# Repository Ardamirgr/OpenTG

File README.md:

<div align="center">

# OpenTG

**Open-source automotive electronics for monitoring, control, ECU communication, and calibration.**

Originally developed for the **Hyundai Coupe / Tiburon**, with many projects designed to be adaptable to other vehicles, ECUs, and custom engine-management setups.

[Support OpenTG](https://www.paypal.com/donate/?hosted_button_id=CYKH5WKZKP4M2)

</div>

---

## Projects

### OpenTG AFR Meter

A complete wideband AFR/lambda system based on the **Bosch LSU 4.9** sensor and **Bosch CJ125** interface IC.

**Wideband controller**

- LSU 4.9 sensor and heater control
- CAN bus output
- Configurable analog AFR/lambda output
- Narrowband and wideband signal emulation

**Digital gauge**

- TFT display with AFR, lambda, oxygen concentration, and sensor-temperature views
- Configurable LED bar
- On-device menu and EEPROM-stored settings
- CAN communication with the controller

---

### OpenTG Boost Controller

A configurable electronic boost-control system for turbocharged vehicles using a MAC-style boost-control solenoid.

- Closed-loop boost control
- Boost targets by RPM and gear
- Multiple selectable boost profiles
- MAP and intake-air-temperature measurement
- CAN-based RPM and vehicle-speed input
- Optional analog inputs
- Overboost protection
- Exhaust-gas-temperature support
- Dedicated TFT gauge and user interface

---

### KLT120 K-Line / L-Line Transceiver

An open-source discrete automotive **K-Line / L-Line transceiver** designed for communication with ECUs and other diagnostic modules using **ISO 9141, ISO 14230 / KWP2000**, and manufacturer-specific K-Line protocols.

Unlike conventional designs based on dedicated K-Line transceiver ICs, the KLT120 uses **LM393B comparators** and discrete N-channel MOSFET line drivers.

Key features include:

* Automotive **K-Line** interface
* Automotive **L-Line** interface
* Independent K-Line and L-Line control
* Selectable **3.3V or 5V MCU logic** depending on the fitted LDO
* Direct interface with microcontroller UART peripherals
* Support for conventional **10.4 kbaud** diagnostic communication
* Support for **5-baud and fast initialization** methods
* Designed for reliable operation at **120 kbaud and beyond**
* Suitable for ECU diagnostics, flashing, logging, and reverse-engineering applications

---

### LTM43 Live Tuning Module

A live-calibration module designed specifically for the **Siemens SIMK43 ECU**.

The LTM43 replaces the original ECU flash memory with a removable module containing:

- **1 Mbit flash memory**, twice the capacity of the original 512 Kbit device
- **512 Kbit SRAM** connected in parallel with the flash memory
- A castellated pin-header adapter PCB that solders directly to the original flash footprint

> [!NOTE]
> The design is based on the live-calibration approach used by Siemens during ECU and engine development.

---

### SLCAN Adapter - Experimental

A compact CAN-to-USB serial interface for ECU flashing, diagnostics, logging, and calibration.

Typical uses include:

- SIMK43 communication
- ECU data logging
- CAN traffic monitoring
- LTM43 live tuning
- Use with compatible OpenTG and OpenGK tools

The adapter implements the **SLCAN protocol**, providing a low-cost alternative to commercial CAN interfaces for supported software.

---

### S4/RS4 MAF Adapter

An adapter board for integrating the Audi S4/RS4 B6 mass-airflow sensors with the stock SIMK43 ECU setups.

It provides a clean interface between the original harness connector and the MAF, without requiring any modifications.

Typical applications include:

- Turbo conversions
- Setups that exceed the measurement range of the original MAF sensor
- Replacement option if the stock MAF sensor can't be found from a reputable manufacturer (VDO, Continental).

---

### R8 COP Adapter

An ignition adapter board for converting the G4GC engines to Audi R8-style coil-on-plug ignition coils. This can theoretically work on any wasted-spark setup.

The board provides an organized interface between the factory engine harness and the replacement coils, simplifying wiring and installation.

> [!IMPORTANT]
> Coil compatibility and ignition strategy must be verified before installation. Depending on the ECU, the ignition dwell times WILL need to be changed, or the R8 Coils will be catastrophically damaged.
> For the G4GC dwell times of <2ms should be used. For most turbocharged setups 1.4-1.6ms is enough.

---

### Oil Temperature / Oil Pressure Gauge

A planned standalone gauge for monitoring engine-oil temperature and pressure.

**Status:** Under development. Have a prototype made from a modified Gauge unit, but no proper hardware design.

---

## Repository Contents

Depending on the project, each directory may include:

| Category | Contents |
|---|---|
| **Hardware** | Schematics, PCB layouts, Gerbers, BOMs, and assembly notes |
| **Firmware** | Embedded source code, binaries, and flashing instructions |
| **Wiring** | Pinouts, connection diagrams, and installation guidance |
| **Calibration** | Configuration files, lookup data, and setup notes |
| **Mechanical** | Enclosure, mounting, or other fabrication files |

Refer to the README inside each project directory for project-specific instructions.

---

## Intended Use

OpenTG projects are intended for enthusiasts, developers, motorsport applications, research, and education.

They may require fine-pitch soldering, ECU disassembly, firmware flashing, automotive electrical knowledge, and engine-management calibration experience.

> [!WARNING]
> Incorrect installation, wiring, firmware, or calibration can damage the ECU, engine, sensors, wiring, or connected equipment. Verify pin assignments, supply voltages, grounding, firmware versions, and board revisions before powering any hardware.

---

## Contributing

Contributions, testing, bug reports, documentation improvements, and hardware revisions are welcome.

For useful bug reports, include the relevant hardware revision, firmware version or commit, vehicle and ECU type, wiring configuration, CAN bitrate, logs or measurements, and a clear description of the problem.

---

## License

See the LICENSE file present in the repository root for license information.

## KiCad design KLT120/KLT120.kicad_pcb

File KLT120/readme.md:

# KLT120

> **Open-source discrete K-Line / L-Line transceiver for 3.3V and 5V microcontrollers**

**KLT120** is a discrete automotive **K-Line / L-Line transceiver** designed for interfacing microcontrollers with **ISO 9141**, **ISO 14230 / KWP2000**, and manufacturer-specific diagnostic buses.

Instead of relying on a dedicated K-Line transceiver IC, KLT120 uses **LM393B comparators** together with discrete **N-channel MOSFET line drivers**.

Depending on the fitted LDO, the logic side of the board can operate at either **3.3V or 5V**, allowing the same PCB to interface with a wide range of microcontrollers.

KLT120 is designed around a **120 kbaud target**, with additional headroom possible depending on bus capacitance, wiring, and the connected ECU. It remains fully suitable for traditional **10.4 kbaud K-Line communication**, **5-baud initialization**, and **fast initialization**.

---

## Features

| Feature | Description |
|---|---|
| **K-Line** | Full transmit and receive support |
| **L-Line** | Independent transmit and receive support |
| **Logic voltage** | 3.3V or 5V, selected by LDO choice |
| **PHY architecture** | LM393B comparators + discrete N-channel MOSFETs |
| **RX threshold** | Battery-referenced, approximately 0.5 × VBAT |
| **Bus pull-up** | Approximately 510–520 Ω tester-side pull-up |
| **Target speed** | 120 kbaud |
| **Protocols** | ISO 9141, ISO 14230 / KWP2000, manufacturer-specific K-Line |
| **Initialization** | 5-baud init and fast init |
| **Supply** | Automotive VBAT with protection and regulated logic rail |

---

## Logic Voltage

KLT120 can be configured for either **3.3V** or **5V** logic by fitting the appropriate LDO.

| LDO | Logic Rail |
|---|---:|
| `TLV7603` | `3.3V` |
| `TLV7605` | `5.0V` |

Throughout the design, this regulated logic rail is referred to as:

```text
VLOGIC
```

The selected logic voltage is used for:

- RX output pull-ups
- TX input logic levels
- Comparator TX reference generation

This allows the same PCB to be used with both modern **3.3V MCUs** and traditional **5V microcontrollers**.

---

## Architecture

Each diagnostic line consists of two main sections:

1. **Transmit driver**
2. **Receive comparator**

K-Line and L-Line are controlled independently.

```text
LM393B #1
├── K-Line TX
└── K-Line RX

LM393B #2
├── L-Line TX
└── L-Line RX
```

L-Line reception is optional in applications where only L-Line transmission is required.

---

## Transmit Path

The transmit stage uses one LM393B comparator as both an **inverter** and **logic-level detector**.

A reference voltage equal to approximately half of the selected logic voltage is generated from `VLOGIC`:

```text
TX_REF ≈ VLOGIC / 2
```

For example:

```text
3.3V logic → TX_REF ≈ 1.65V
5.0V logic → TX_REF ≈ 2.50V
```

The MCU transmit signal is connected to the inverting comparator input:

```text
MCU TX  -------- LM393B (-)
TX_REF  -------- LM393B (+)
```

Because the LM393B output is **open collector**, the MOSFET gate pull-up voltage can be chosen independently from the comparator supply voltage.

The comparator output drives an N-channel MOSFET used as a low-side K/L-Line switch.

### TX Logic

| MCU TX | MOSFET | K/L Line |
|---:|:---:|:---:|
| `HIGH` | OFF | HIGH / released |
| `LOW` | ON | LOW / dominant |

This preserves normal UART polarity.

When UART TX is idle (`HIGH`), the MOSFET remains OFF and the diagnostic line is released.

---

## K-Line / L-Line Output Stage

Each diagnostic line is pulled toward vehicle battery voltage through approximately **510–520 Ω** on the tester side.

The pull-up is implemented using **three 1206 resistors in series** to spread the power dissipation.

```text
VBAT
 |
~510–520 Ω
 |
 +------------- K/L LINE
 |
Drain
 NMOS
Source
 |
GND
```

At a vehicle charging voltage of **14.5V** and a **520 Ω** pull-up:

```text
I = 14.5 / 520
I ≈ 27.9 mA

P = V² / R
P ≈ 0.40 W
```

The line-driver MOSFET therefore only needs to sink roughly **30 mA** during a dominant LOW state.

Suitable SOT-23 N-channel MOSFETs include:

- `2N7002K`
- `BSS123`

Important MOSFET characteristics are:

- Sufficient `VDS` rating
- Sufficient `VGS` rating
- Low gate charge
- Ability to sink at least ~30 mA
- Suitable switching behavior at the selected gate voltage

Very low `RDS(on)` is not required because the bus current is relatively small.

---

## Receiver

The receive stage uses the second comparator in each LM393B.

Instead of comparing the diagnostic line against a fixed voltage, the receiver threshold is derived from **VBAT**. This keeps the switching point proportional to the actual K/L-Line HIGH level.

The diagnostic-line input is divided before reaching the comparator:

```text
VLINE_SENSE = VLINE / 4
```

The reference input is derived from VBAT:

```text
VREF = VBAT / 8
```

The comparator changes state when:

```text
VLINE / 4 = VBAT / 8
```

Therefore:

```text
VLINE = VBAT / 2
```

So the resulting receive threshold is approximately:

```text
VTH ≈ 0.5 × VBAT
```

This battery-referenced threshold is similar in principle to the input architecture used by dedicated automotive K-Line transceiver ICs.

---

## RX Logic Output

Because the LM393B output is **open collector**, the RX output can be pulled directly to the selected logic rail.

Depending on the fitted LDO, the MCU therefore receives either:

```text
0 / 3.3V
```

or:

```text
0 / 5.0V
```

No additional RX level shifter is required.

---

## K-Line and L-Line

K-Line is normally used for bidirectional communication between the diagnostic tester and ECU.

L-Line is primarily associated with initialization and wake-up on older ISO 9141 / KWP2000 systems.

KLT120 keeps both lines independent, allowing firmware to implement:

- K-Line-only communication
- K + L initialization
- 5-baud initialization
- Fast initialization
- Manufacturer-specific wake-up sequences
- Independent K-Line / L-Line monitoring

For applications that do not require L-Line reception, the `L_RX` comparator may be left unused.

---

## Baud Rate

KLT120 is designed around a target communication speed of:

```text
120 kbaud
```

At 120000 baud:

```text
Tbit = 1 / 120000
Tbit ≈ 8.33 µs
```

The LM393B propagation delay under large input overdrive is on the order of hundreds of nanoseconds, while the MOSFET switching time is significantly shorter.

The main limitation at higher baud rates is normally the **LOW-to-HIGH transition** of the diagnostic bus.

When the MOSFET releases the line, the pull-up resistor must charge the total bus capacitance.

The approximate RC time constant is:

```text
τ = R × C
```

With a 510–520 Ω pull-up:

| Bus Capacitance | Approx. RC Time Constant |
|---:|---:|
| `1 nF` | `~0.52 µs` |
| `5 nF` | `~2.60 µs` |
| `10 nF` | `~5.20 µs` |

The actual maximum usable baud rate depends on:

- Vehicle wiring
- Diagnostic cable length
- ECU input capacitance
- Protection components
- Connector capacitance
- Number of devices connected to the bus

Traditional **10.4 kbaud** K-Line operation has a very large timing margin.

> **120 kbaud is the intended design target, not a guarantee for every possible vehicle harness.**

---

## Why a Discrete Transceiver?

Dedicated K-Line transceiver ICs are convenient, but some parts can be difficult to source, relatively expensive, or inconvenient when working with configurable MCU logic levels.

KLT120 implements the basic automotive diagnostic PHY using common components:

```text
Comparator
    +
MOSFET
    +
Resistors
    +
Protection
```

This makes the design:

- Easy to understand
- Easy to modify
- Easy to repair
- Flexible with component selection
- Compatible with both 3.3V and 5V systems
- Well suited to custom diagnostic hardware

It also allows the receive threshold, output drive, pull-up strength, and protection circuitry to be adapted for specific applications.

---

## Applications

KLT120 can be used for:

- Automotive diagnostic interfaces
- ECU flashing tools
- ECU reverse engineering
- KWP2000 communication
- ISO 9141 communication
- ECU bench harnesses
- ESP32-based diagnostic tools
- AVR-based diagnostic tools
- STM32-based diagnostic tools
- Data logging equipment
- Manufacturer-specific K-Line protocols
- 5-baud initialization
- Fast initialization
- Development and research hardware

---

## Project Status

> **KLT120 is currently under development.**

The hardware should be considered experimental until it has been validated against multiple ECUs, vehicles, wiring configurations, baud rates, and automotive transient conditions.

Testing is intended to cover both standard KWP2000 communication speeds and higher-speed K-Line implementations.

---

## Disclaimer

This project is intended for **development, research, diagnostic, and educational use**.

Automotive electrical systems can generate high-energy voltage transients. Incorrect connections may damage the interface, ECU, vehicle electronics, or connected development hardware.

**Use at your own risk.**

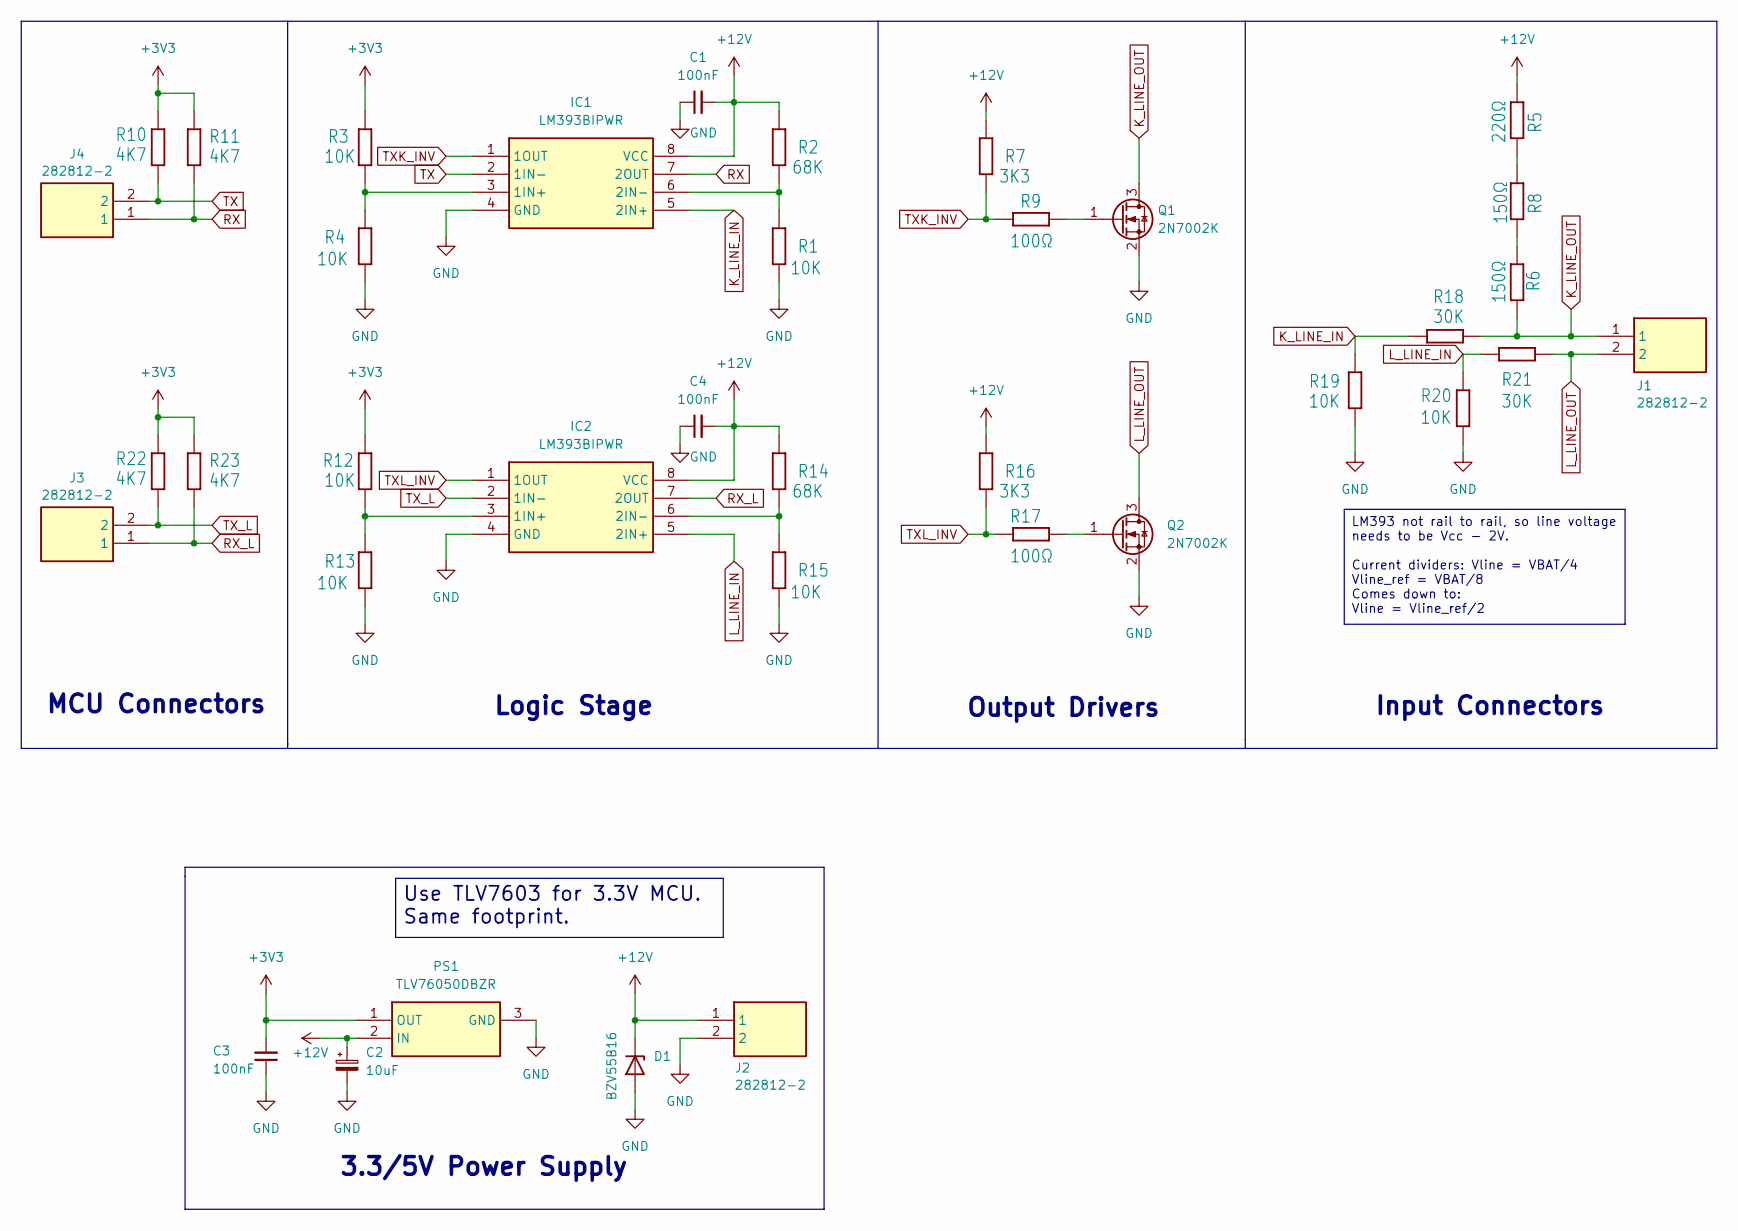
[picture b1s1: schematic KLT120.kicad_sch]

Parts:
C1, C3, C4: 100nF; C_0805_2012Metric
C2: 10uF; CP_Elec_5x5.7
D1: BZV55B16; D_MiniMELF
IC1, IC2: LM393BIPWR; SOP65P640X120-8N; Mouser Part Number 595-LM393BIPWR
J1, J2, J3, J4: 282812-2; 2828122; Mouser Part Number 571-282812-2
PS1: TLV76050DBZR; SOT95P237X112-3N; Mouser Part Number 595-TLV76050DBZR
Q1, Q2: 2N7002K; SOT-23
R1, R3, R4, R12, R13, R15, R19, R20: 10K; R_0805_2012Metric_Pad1.20x1.40mm_HandSolder
R2, R14: 68K; R_0805_2012Metric_Pad1.20x1.40mm_HandSolder
R5: 220Ω; R_1206_3216Metric_Pad1.30x1.75mm_HandSolder
R6, R8: 150Ω; R_1206_3216Metric_Pad1.30x1.75mm_HandSolder
R7, R16: 3K3; R_0805_2012Metric_Pad1.20x1.40mm_HandSolder
R9, R17: 100Ω; R_0805_2012Metric_Pad1.20x1.40mm_HandSolder
R10, R11, R22, R23: 4K7; R_0805_2012Metric_Pad1.20x1.40mm_HandSolder
R18, R21: 30K; R_0805_2012Metric_Pad1.20x1.40mm_HandSolder

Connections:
+3V3: C3.2, PS1.1 (OUT), R3.2, R10.2, R11.2, R12.2, R22.2, R23.2
+12V: C1.2, C2.1, C4.2, D1.1 (K), IC1.8 (VCC), IC2.8 (VCC), J2.1, PS1.2 (IN), R2.2, R5.2, R7.2, R14.2, R16.2
GND: C1.1, C2.2, C3.1, C4.1, D1.2 (A), IC1.4 (GND), IC2.4 (GND), J2.2, PS1.3 (GND), Q1.2 (S), Q2.2 (S), R1.1, R4.1, R13.1, R15.1, R19.1, R20.1
K_LINE_IN: IC1.5 (2IN+), R18.2, R19.2
K_LINE_OUT: J1.1, Q1.3 (D), R6.1, R18.1
L_LINE_IN: IC2.5 (2IN+), R20.2, R21.2
L_LINE_OUT: J1.2, Q2.3 (D), R21.1
unnamed: IC1.3 (1IN+), R3.1, R4.2
unnamed: IC1.6 (2IN-), R1.2, R2.1
unnamed: IC2.3 (1IN+), R12.1, R13.2
unnamed: IC2.6 (2IN-), R14.1, R15.2
unnamed: Q1.1 (G), R9.1
unnamed: Q2.1 (G), R17.1
unnamed: R5.1, R8.2
unnamed: R6.2, R8.1
RX: IC1.7 (2OUT), J4.1, R11.1
RX_L: IC2.7 (2OUT), J3.1, R23.1
TX: IC1.2 (1IN-), J4.2, R10.1
TXK_INV: IC1.1 (1OUT), R7.1, R9.2
TXL_INV: IC2.1 (1OUT), R16.1, R17.2
TX_L: IC2.2 (1IN-), J3.2, R22.1

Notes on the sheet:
Output Drivers
Logic Stage
Input Connectors
MCU Connectors
3.3/5V Power Supply
LM393 not rail to rail, so line voltage needs to be Vcc - 2V. Current dividers: Vline = VBAT/4 Vline_ref = VBAT/8 Comes down to: Vline = Vline_ref/2
Use TLV7603 for 3.3V MCU. Same footprint.

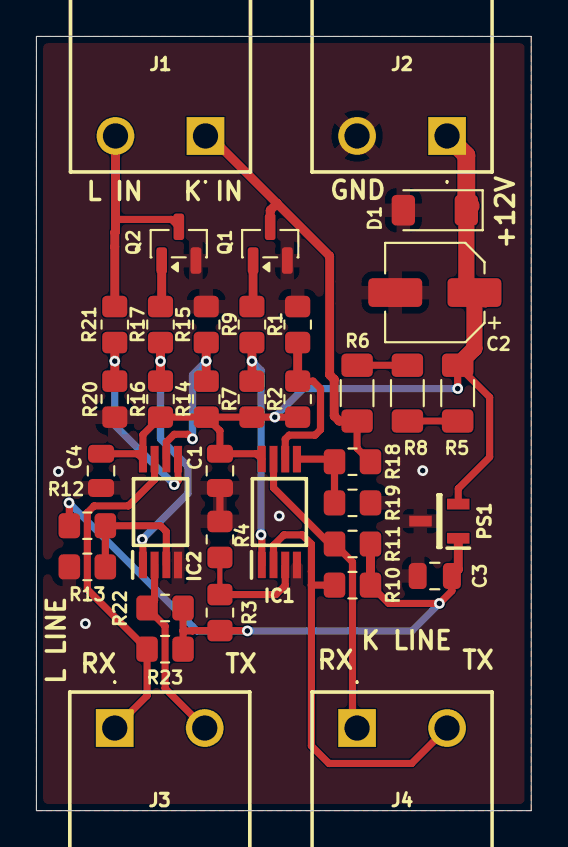
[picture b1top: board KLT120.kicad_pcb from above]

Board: 2 copper layers, 27.5 x 43.0 mm, 37 parts (0 on the bottom side), 21 nets.

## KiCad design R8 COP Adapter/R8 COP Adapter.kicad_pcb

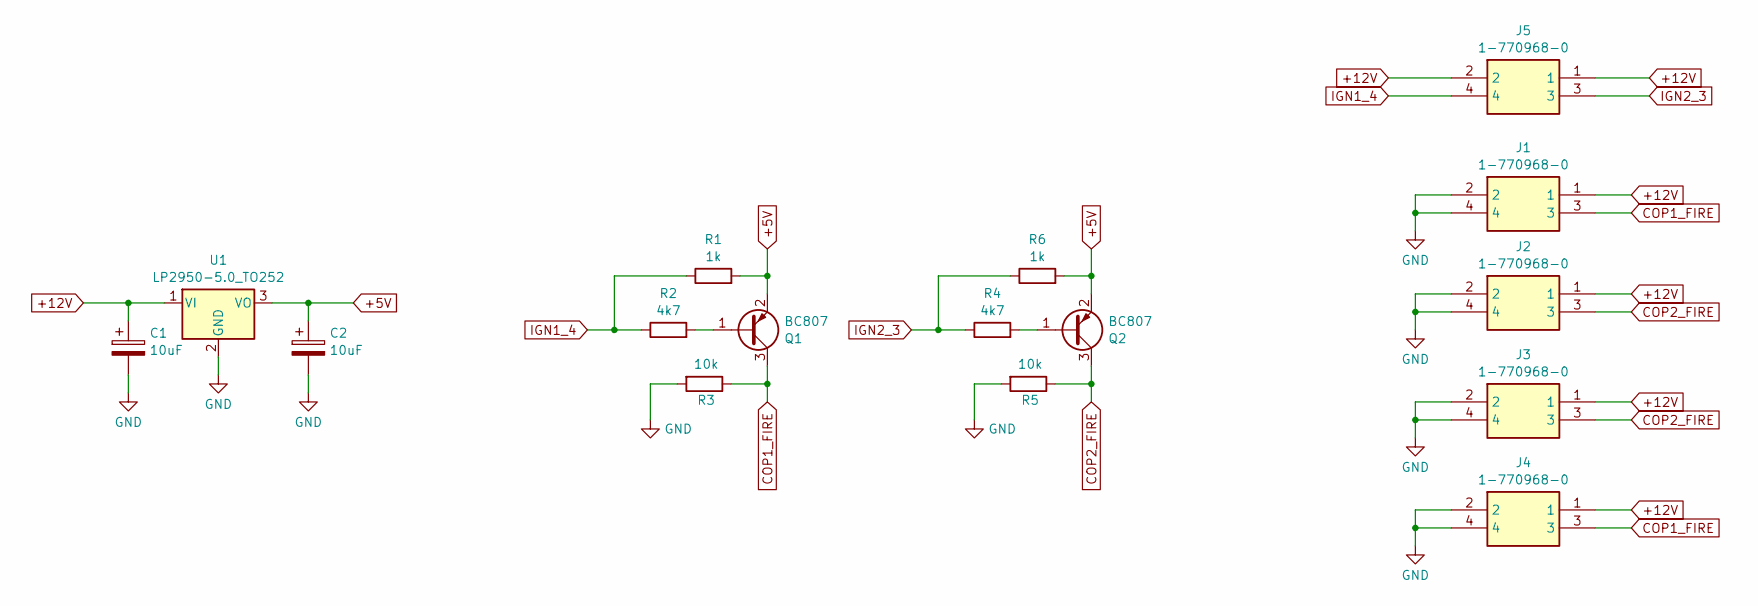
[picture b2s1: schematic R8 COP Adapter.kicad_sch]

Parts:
C1, C2: 10uF; CP_Radial_D5.0mm_P2.00mm
J1, J2, J3, J4, J5: 1-770968-0; 17709680; Mouser Part Number 571-1-770968-0
Q1, Q2: BC807; SOT-23
R1, R6: 1k; R_0805_2012Metric
R2, R4: 4k7; R_0805_2012Metric
R3, R5: 10k; R_0805_2012Metric
U1: LP2950-5.0_TO252; TO-252-2

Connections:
+5V: C2.1, Q1.2 (E), Q2.2 (E), R1.2, R6.2, U1.3 (VO)
+12V: C1.1, J1.1, J2.1, J3.1, J4.1, J5.1, J5.2, U1.1 (VI)
COP1_FIRE: J1.3, J4.3, Q1.3 (C), R3.1
COP2_FIRE: J2.3, J3.3, Q2.3 (C), R5.1
GND: C1.2, C2.2, J1.2, J1.4, J2.2, J2.4, J3.2, J3.4, J4.2, J4.4, R3.2, R5.2, U1.2 (GND); also elsewhere on the board
IGN1_4: J5.4, R1.1, R2.1
IGN2_3: J5.3, R4.1, R6.1
unnamed: Q1.1 (B), R2.2
unnamed: Q2.1 (B), R4.2

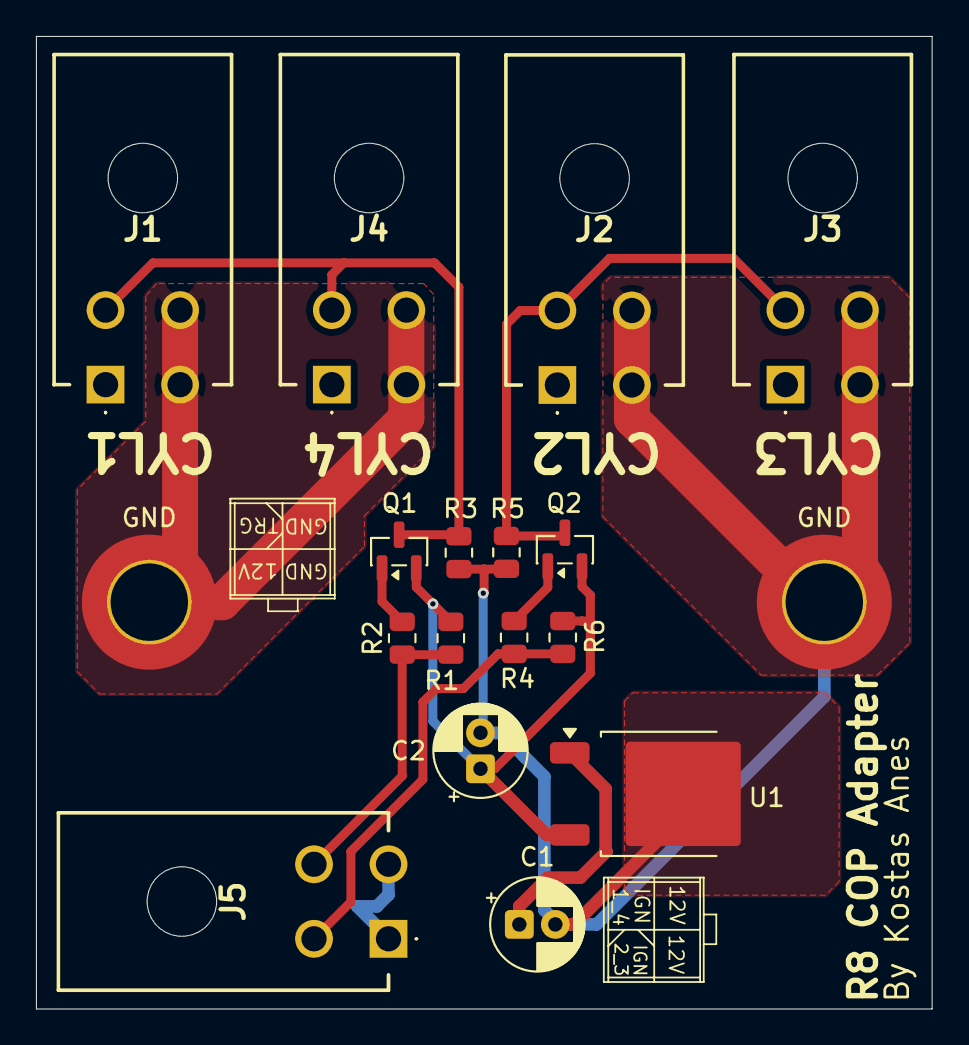
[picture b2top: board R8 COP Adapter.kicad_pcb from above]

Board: 2 copper layers, 49.8 x 54.0 mm, 18 parts (0 on the bottom side), 9 nets.

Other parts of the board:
GND: MountingHole_4.3mm_M4_DIN965_Pad_TopBottom
GND#2: MountingHole_4.3mm_M4_DIN965_Pad_TopBottom

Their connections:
GND: GND.1, GND#2.1; also elsewhere on the board

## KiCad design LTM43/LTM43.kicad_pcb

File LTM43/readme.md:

# LTM43 — Live Tuning Module for the Siemens SIMK43 ECU

LTM43 is a hardware module that enables live calibration changes on Siemens SIMK43 engine control units.

The module replaces the original flash memory fitted to the ECU. A small pin-header adapter PCB is soldered directly onto the original flash IC footprint, and the LTM43 plugs into this adapter through female headers.

> [!WARNING]
> This project requires fine-pitch soldering directly onto an automotive ECU PCB. Incorrect assembly, wiring, flashing, or use may permanently damage the ECU or prevent the engine from starting. Use the module only if you are familiar with ECU repair, boot-mode flashing, and automotive electrical systems.

## How It Works

The LTM43 contains:

- A **1 Mbit flash memory**, providing twice the capacity of the original 512 Kbit device.
- A **512 Kbit SRAM**, connected in parallel with the flash memory.

When the ECU starts in the required debug mode, the calibration data is copied from flash into SRAM. The ECU then operates from the SRAM copy, allowing calibration data to be modified while the ECU is running.

During shutdown, the modified SRAM contents are copied back into flash. The updated calibration is therefore retained and restored at the next startup.

This follows the live-tuning method used by Siemens during ECU and engine development.

## Hardware Overview

The system consists of two PCBs:

1. **Flash adapter board**  
   Soldered directly to the original flash IC pads on the SIMK43 ECU.

2. **LTM43 module**  
   Plugs into the adapter board through female pin headers and contains the replacement flash and SRAM devices.

## SRAM Options

The LTM43 PCB includes alternative SRAM footprints to support different packages. During assembly, populate **only one SRAM option**.

Supported devices are:

- Infineon `CY62128ELL-45ZXI`
- Infineon `CY62128ELL-45SXA`
- Renesas `R1LP0108ESN-5SI#B1`

## Board Assembly

The pin-header adapter board must sit completely flush against the ECU PCB so that its castellated edges can be soldered correctly to the original flash IC pads.

After installing and trimming the pin headers:

1. Cut the protruding header pins as close to the adapter PCB as practical.
2. Carefully sand the remaining pin ends until they are level with the underside of the PCB.
3. Confirm that no pin end prevents the adapter board from sitting flat.

For the LTM43 module, just solder the IC's and 100nF capacitors at their respective footprints. 
Remeber that the female headers should be placed on the bottom PCB side! 

> [!CAUTION]
> Do not force the adapter board flat while soldering. Any remaining pin protrusion can place mechanical stress on the ECU pads and may cause pad lifting or unreliable connections.

## Installation

1. Remove the original flash IC from the SIMK43 ECU.
2. Clean and inspect the exposed flash footprint.
3. Assemble the pin-header adapter as described above.
4. Align the castellated pads with the original flash footprint.
5. Check orientation and pin numbering before soldering (Pin#1 should be at the side of the C167 MCU).
6. Solder the adapter board to the ECU flash pads.
7. Solder a jumper wire from C167 Pin 88 (P4.3/A19 ) to the Adapter Board pin #3. This is best done from a via present on the bottom side of the ECU, that connects to Pin 88. 
8. Inspect every connection for bridges, incomplete joints, lifted pads, or misalignment.
9. Insert the LTM43 to the pin headers of the adapter board, observing the correct orientation (LTM43 oriented towards C167 MCU).
10. Perform an initial BSL flash to program the replacement flash memory.

## Initial BSL Flash

A blank replacement flash device must first be programmed through the SIMK43 boot-strapped loader, or **BSL**, interface.

The required firmware is:

```text
ca663057
```

It is available from the OpenGK SIMK repository:

- [OpenGK SIMK firmware repository](https://github.com/OpenGK-org/opengk-simk)

GKFlasher can be used to BSL flash and it is available here:

- [GKFlasher releases](https://github.com/Dante383/GKFlasher/releases)

### BSL Connection Method 1

1. Connect ECU pins **3, 14, 21, and 22** to **+12 V**.
2. Connect the diagnostic **K-Line** to ECU pin **77**, according to the ECU pinout.
3. Fit a **470 Ω resistor** to the ECU **W-Line**.
4. Splice the K-Line into the K-Line connection on the ECU header. When using a Y-split OBD2 cable, this is pin **9**.
5. Pull the **BOOT** pin to ground through a **10 kΩ resistor**.
6. Connect ECU power and ground.
7. Open the **BSL** tab in GKFlasher and begin the required operation.

### Alternative BSL Connection Method

Use this method when the first connection method does not work:

1. Connect ECU pins **3, 14, 21, and 22** to **+12 V**.
2. Connect OBD pin **7**, the K-Line, to ECU header pin **47**, the W-Line.
3. Pull flash-memory pin **28**, the BOOT pin, to ground through a **10 kΩ resistor**.
4. Connect ECU power and ground.
5. Open the **BSL** tab in GKFlasher and begin the required operation.

> [!IMPORTANT]
> Verify all ECU pin numbers against the correct SIMK43 connector and PCB documentation before applying power. Use a current-limited, fused 12 V supply for bench flashing.

## CAN Bus Communication

After the initial BSL flash, subsequent communication and calibration changes can be performed through CAN bus.

Supported interfaces include:

- A PCAN-compatible interface
- The OpenTG SLCAN Adapter

SLCAN Adapter project:

- [OpenTG SLCAN Adapter](https://github.com/Ardamirgr/OpenTG/tree/main/SLCAN_Adapter)

### CAN Wiring

Connect:

| Signal | SIMK43 ECU pin |
|---|---:|
| CAN High | 7 |
| CAN Low | 6 |
| Ground | ECU/interface shared ground |

A shared ground between the ECU and CAN interface is required.

### SLCAN Adapter Power

The SLCAN Adapter requires a regulated **5V supply**. It can be powered by either:

- The USB header, when the corresponding power-selection jumper is shorted.
- An external regulated 5V source, such as a suitable ECU-side supply.

Do not apply 12V directly to a 5V input.

## Recommended First Power-Up Procedure

Before connecting the ECU to a vehicle:

1. Inspect the adapter and LTM43 for solder bridges and incorrect component orientation.
2. Check resistance between all supply rails and ground for obvious short circuits.
3. Verify continuity from every ECU flash pad to the corresponding LTM43 signal.
5. Power the ECU from a fused, current-limited bench supply.
6. Perform the BSL flash using the `ca663057` firmware.
7. Power-cycle the ECU and verify CAN communication.
8. Confirm that calibration reads and writes operate correctly before vehicle installation.

## Removal and Serviceability

The LTM43 is removable after the flash-footprint adapter has been installed. This allows the module to be replaced or serviced without repeatedly soldering directly to the ECU flash pads.

Always disconnect ECU power before inserting or removing the LTM43.

## Disclaimer

This project is intended for development, research, motorsport, and off-road applications by experienced users.

The project contributors accept no responsibility for:

- ECU, engine, wiring, or vehicle damage
- Data corruption or failed flashing
- Unsafe engine calibration
- Emissions or road-legality violations
- Injury or property damage resulting from assembly or use

You are responsible for verifying the hardware, firmware, wiring, calibration, and legal suitability of the finished system.

## Related Projects

- [OpenGK SIMK](https://github.com/OpenGK-org/opengk-simk)
- [GKFlasher](https://github.com/Dante383/GKFlasher/releases)
- [OpenTG SLCAN Adapter](https://github.com/Ardamirgr/OpenTG/tree/main/SLCAN_Adapter)

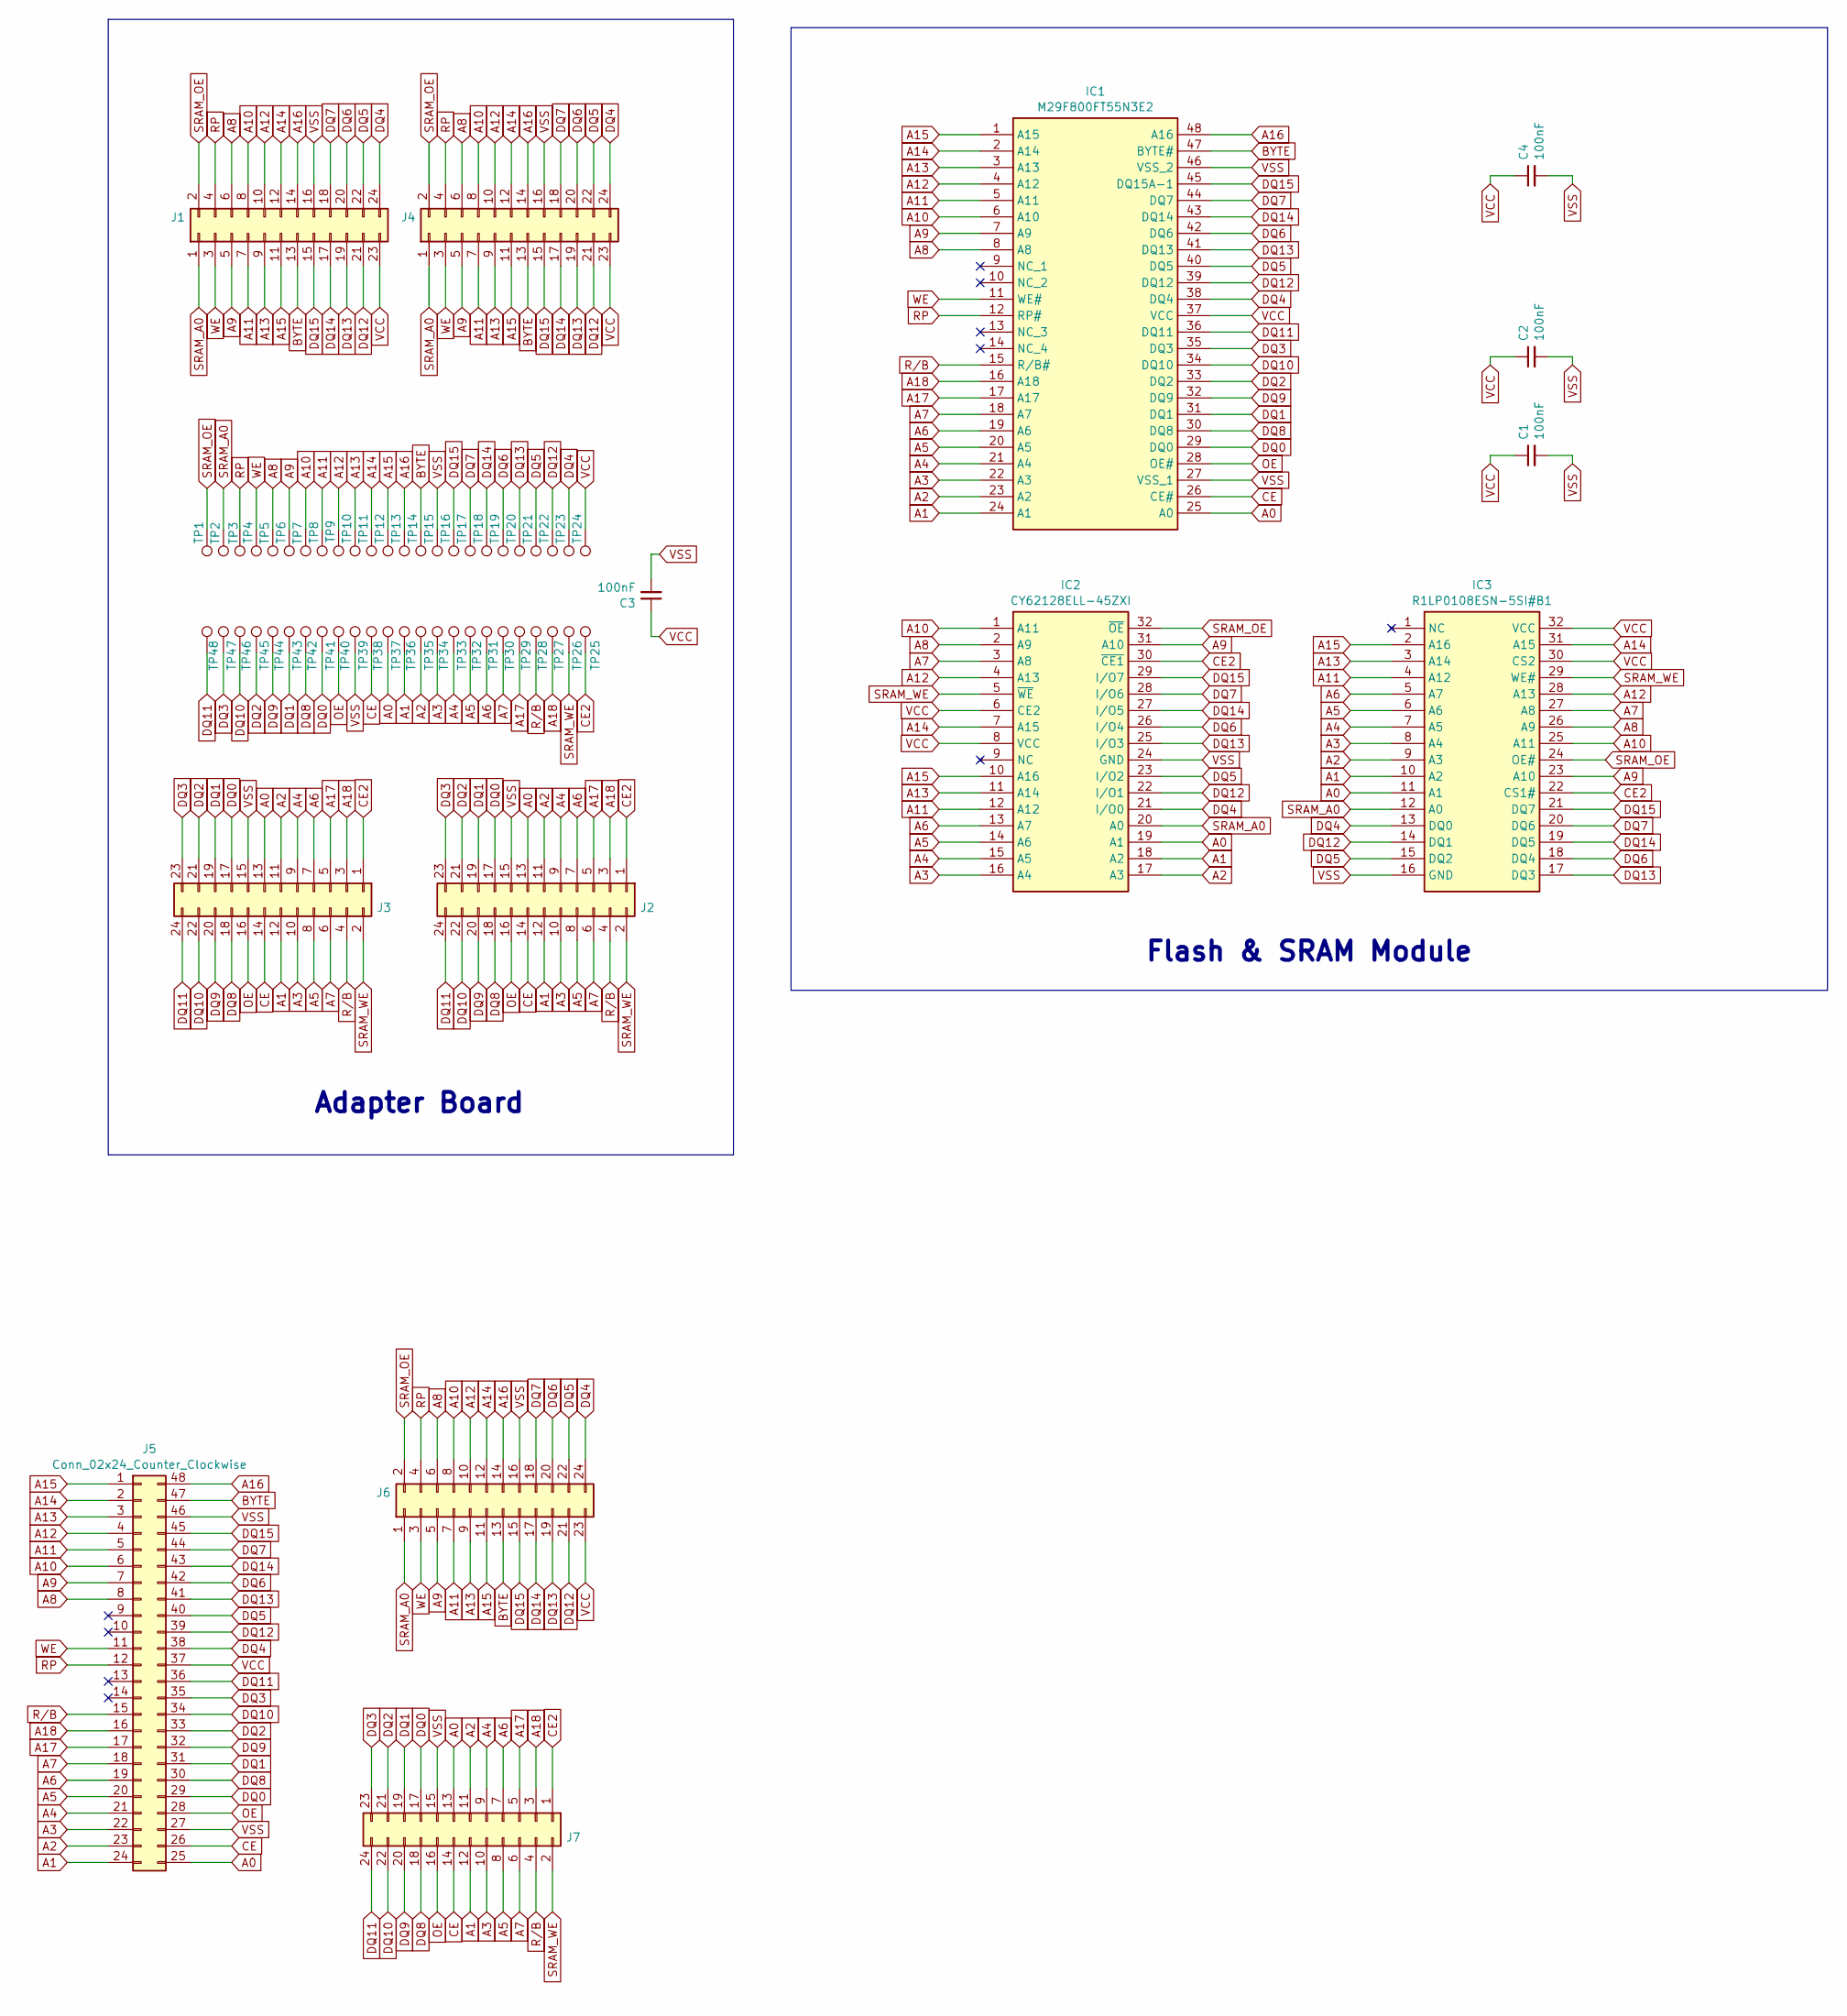
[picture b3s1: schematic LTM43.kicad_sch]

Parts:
C1, C2, C3, C4: 100nF; C_0805_2012Metric
IC1: M29F800FT55N3E2; SOP50P2000X120-48N; Mouser Part Number 913-M29F800FT55N3E2
IC2: CY62128ELL-45ZXI; SOP50P2000X120-32N; Mouser Part Number 727-CY62128ELL45ZXI
IC3: R1LP0108ESN-5SI#B1; SOIC127P1410X305-32N; Mouser Part Number 968-R1LP0108ESN5SIB1
J1, J2: Conn_02x12_Odd_Even
J3, J4: Conn_02x12_Odd_Even; PinSocket_2x12_P2.54mm_Vertical
J5: Conn_02x24_Counter_Clockwise; DIP-48_W15.24mm_Socket_LongPads
J6, J7: Conn_02x12_Odd_Even; PinHeader_2x12_P2.54mm_Vertical
TP1, TP2, TP3, TP4, TP5, TP6, TP7, TP8, TP9, TP10, TP11, TP12, TP13, TP14, TP15, TP16, TP17, TP18, TP19, TP20, TP21, TP22, TP23, TP24: TestPoint; TestPoint_THTPad_D1.0mm_Drill0.5mm
TP25, TP26, TP27, TP28, TP29, TP30, TP31, TP32, TP33, TP34, TP35, TP36, TP37, TP38, TP39, TP40, TP41, TP42, TP43, TP44, TP45, TP46, TP47, TP48: TestPoint

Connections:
A0: IC1.25 (A0), IC2.19 (A1), IC3.11 (A1), J2.13, J3.13, J5.25, J7.13, TP37.1 (1_1)
A1: IC1.24 (A1), IC2.18 (A2), IC3.10 (A2), J2.12, J3.12, J5.24, J7.12, TP36.1 (1_1)
A2: IC1.23 (A2), IC2.17 (A3), IC3.9 (A3), J2.11, J3.11, J5.23, J7.11, TP35.1 (1_1)
A3: IC1.22 (A3), IC2.16 (A4), IC3.8 (A4), J2.10, J3.10, J5.22, J7.10, TP34.1 (1_1)
A4: IC1.21 (A4), IC2.15 (A5), IC3.7 (A5), J2.9, J3.9, J5.21, J7.9, TP33.1 (1_1)
A5: IC1.20 (A5), IC2.14 (A6), IC3.6 (A6), J2.8, J3.8, J5.20, J7.8, TP32.1 (1_1)
A6: IC1.19 (A6), IC2.13 (A7), IC3.5 (A7), J2.7, J3.7, J5.19, J7.7, TP31.1 (1_1)
A7: IC1.18 (A7), IC2.3 (A8), IC3.27 (A8), J2.6, J3.6, J5.18, J7.6, TP30.1 (1_1)
A8: IC1.8 (A8), IC2.2 (A9), IC3.26 (A9), J1.6, J4.6, J5.8, J6.6, TP5.1 (1_1)
A9: IC1.7 (A9), IC2.31 (A10), IC3.23 (A10), J1.5, J4.5, J5.7, J6.5, TP6.1 (1_1)
A10: IC1.6 (A10), IC2.1 (A11), IC3.25 (A11), J1.8, J4.8, J5.6, J6.8, TP7.1 (1_1)
A11: IC1.5 (A11), IC2.12 (A12), IC3.4 (A12), J1.7, J4.7, J5.5, J6.7, TP8.1 (1_1)
A12: IC1.4 (A12), IC2.4 (A13), IC3.28 (A13), J1.10, J4.10, J5.4, J6.10, TP9.1 (1_1)
A13: IC1.3 (A13), IC2.11 (A14), IC3.3 (A14), J1.9, J4.9, J5.3, J6.9, TP10.1 (1_1)
A14: IC1.2 (A14), IC2.7 (A15), IC3.31 (A15), J1.12, J4.12, J5.2, J6.12, TP11.1 (1_1)
A15: IC1.1 (A15), IC2.10 (A16), IC3.2 (A16), J1.11, J4.11, J5.1, J6.11, TP12.1 (1_1)
A16: IC1.48 (A16), J1.14, J4.14, J5.48, J6.14, TP13.1 (1_1)
A17: IC1.17 (A17), J2.5, J3.5, J5.17, J7.5, TP29.1 (1_1)
A18: IC1.16 (A18), J2.3, J3.3, J5.16, J7.3, TP27.1 (1_1)
BYTE: IC1.47 (BYTE#), J1.13, J4.13, J5.47, J6.13, TP14.1 (1_1)
CE: IC1.26 (CE#), J2.14, J3.14, J5.26, J7.14, TP38.1 (1_1)
CE2: IC2.30 (~CE1), IC3.22 (CS1#), J2.1, J3.1, J7.1, TP25.1 (1_1)
DQ0: IC1.29 (DQ0), J2.17, J3.17, J5.29, J7.17, TP41.1 (1_1)
DQ1: IC1.31 (DQ1), J2.19, J3.19, J5.31, J7.19, TP43.1 (1_1)
DQ2: IC1.33 (DQ2), J2.21, J3.21, J5.33, J7.21, TP45.1 (1_1)
DQ3: IC1.35 (DQ3), J2.23, J3.23, J5.35, J7.23, TP47.1 (1_1)
DQ4: IC1.38 (DQ4), IC2.21 (I/O0), IC3.13 (DQ0), J1.24, J4.24, J5.38, J6.24, TP23.1 (1_1)
DQ5: IC1.40 (DQ5), IC2.23 (I/O2), IC3.15 (DQ2), J1.22, J4.22, J5.40, J6.22, TP21.1 (1_1)
DQ6: IC1.42 (DQ6), IC2.26 (I/O4), IC3.18 (DQ4), J1.20, J4.20, J5.42, J6.20, TP19.1 (1_1)
DQ7: IC1.44 (DQ7), IC2.28 (I/O6), IC3.20 (DQ6), J1.18, J4.18, J5.44, J6.18, TP17.1 (1_1)
DQ8: IC1.30 (DQ8), J2.18, J3.18, J5.30, J7.18, TP42.1 (1_1)
DQ9: IC1.32 (DQ9), J2.20, J3.20, J5.32, J7.20, TP44.1 (1_1)
DQ10: IC1.34 (DQ10), J2.22, J3.22, J5.34, J7.22, TP46.1 (1_1)
DQ11: IC1.36 (DQ11), J2.24, J3.24, J5.36, J7.24, TP48.1 (1_1)
DQ12: IC1.39 (DQ12), IC2.22 (I/O1), IC3.14 (DQ1), J1.21, J4.21, J5.39, J6.21, TP22.1 (1_1)
DQ13: IC1.41 (DQ13), IC2.25 (I/O3), IC3.17 (DQ3), J1.19, J4.19, J5.41, J6.19, TP20.1 (1_1)
DQ14: IC1.43 (DQ14), IC2.27 (I/O5), IC3.19 (DQ5), J1.17, J4.17, J5.43, J6.17, TP18.1 (1_1)
DQ15: IC1.45 (DQ15A-1), IC2.29 (I/O7), IC3.21 (DQ7), J1.15, J4.15, J5.45, J6.15, TP16.1 (1_1)
OE: IC1.28 (OE#), J2.16, J3.16, J5.28, J7.16, TP40.1 (1_1)
RP: IC1.12 (RP#), J1.4, J4.4, J5.12, J6.4, TP3.1 (1_1)
R/B: IC1.15 (R/B#), J2.4, J3.4, J5.15, J7.4, TP28.1 (1_1)
SRAM_A0: IC2.20 (A0), IC3.12 (A0), J1.1, J4.1, J6.1, TP2.1 (1_1)
SRAM_OE: IC2.32 (~OE), IC3.24 (OE#), J1.2, J4.2, J6.2, TP1.1 (1_1)
SRAM_WE: IC2.5 (~WE), IC3.29 (WE#), J2.2, J3.2, J7.2, TP26.1 (1_1)
VCC: C1.1, C2.1, C3.1, C4.1, IC1.37 (VCC), IC2.6 (CE2), IC2.8 (VCC), IC3.30 (CS2), IC3.32 (VCC), J1.23, J4.23, J5.37, J6.23, TP24.1 (1_1)
VSS: C1.2, C2.2, C3.2, C4.2, IC1.27 (VSS_1), IC1.46 (VSS_2), IC2.24 (GND), IC3.16 (GND), J1.16, J2.15, J3.15, J4.16, J5.27, J5.46, J6.16, J7.15, TP15.1 (1_1), TP39.1 (1_1)
WE: IC1.11 (WE#), J1.3, J4.3, J5.11, J6.3, TP4.1 (1_1)

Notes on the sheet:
Flash & SRAM Module
Adapter Board
